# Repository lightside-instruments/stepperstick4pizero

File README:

stepperstick4pizero is an open hardware platform for FPGA
development published by Lightside Instruments AS.

The initial release stepperstick4pizero-1.0 includes schematic and PCB
design files for KiCAD.

The project is published by Lightside Instruments AS
under TAPR Open Hardware License. Read the LICENSE file
for details.

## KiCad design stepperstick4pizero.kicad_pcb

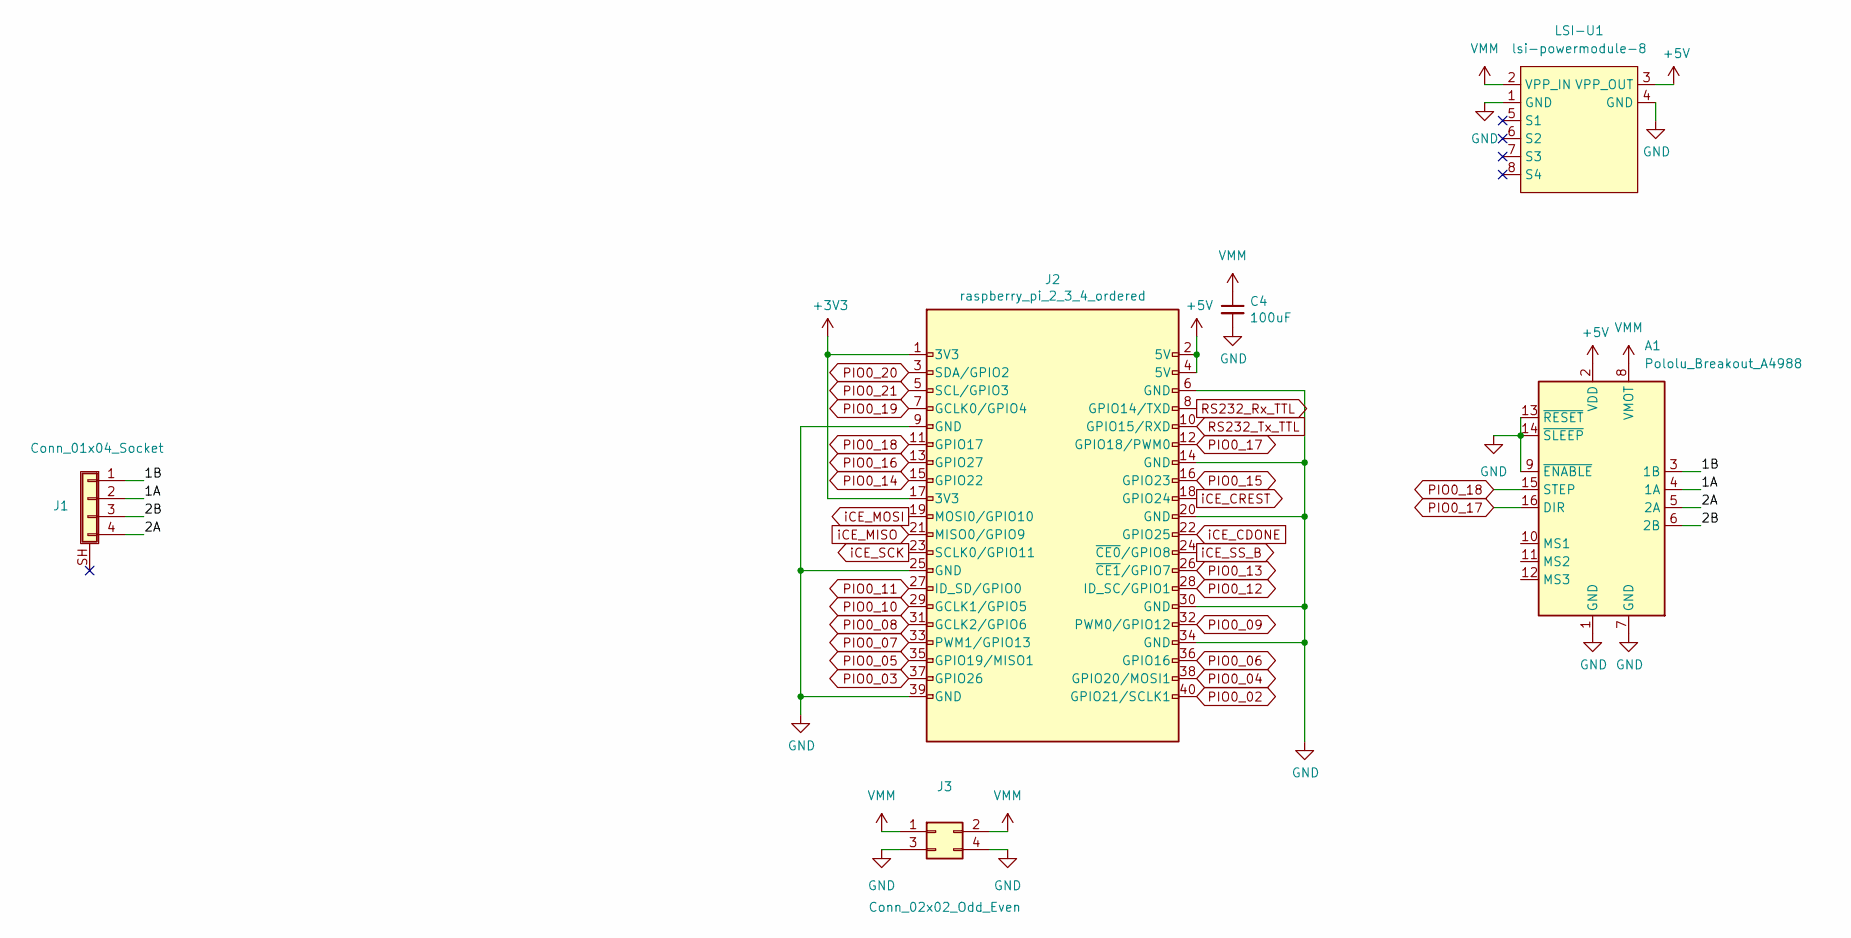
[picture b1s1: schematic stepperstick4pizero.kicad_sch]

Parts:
A1: Pololu_Breakout_A4988; Pololu_Breakout-16_15.2x20.3mm
C4: 100uF; C_Elec_6.3x7.7
J1: Conn_01x04_Socket; Amphenol_M8S-04PMMR-SF8001
J2: raspberry_pi_2_3_4_ordered; PinSocket_2x20_P2.54mm_Vertical_1_04mm
J3: Conn_02x02_Odd_Even; PinHeader_2x02_P2.54mm_Vertical
LSI-U1: lsi-powermodule-8

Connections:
+3V3: J2.1 (3V3), J2.17 (3V3)
+5V: A1.2 (VDD), J2.2 (5V), J2.4 (5V), LSI-U1.3 (VPP_OUT)
/1A: A1.4 (1A), J1.2
/1B: A1.3 (1B), J1.1
/2A: A1.5 (2A), J1.4
/2B: A1.6 (2B), J1.3
GND: A1.1 (GND), A1.7 (GND), A1.9 (~ENABLE), A1.13 (~RESET), A1.14 (~SLEEP), C4.2, J2.6 (GND), J2.9 (GND), J2.14 (GND), J2.20 (GND), J2.25 (GND), J2.30 (GND), J2.34 (GND), J2.39 (GND), J3.3, J3.4, LSI-U1.1 (GND), LSI-U1.4 (GND)
PIO0_02: J2.40 (GPIO21/SCLK1)
PIO0_03: J2.37 (GPIO26)
PIO0_04: J2.38 (GPIO20/MOSI1)
PIO0_05: J2.35 (GPIO19/MISO1)
PIO0_06: J2.36 (GPIO16)
PIO0_07: J2.33 (PWM1/GPIO13)
PIO0_08: J2.31 (GCLK2/GPIO6)
PIO0_09: J2.32 (PWM0/GPIO12)
PIO0_10: J2.29 (GCLK1/GPIO5)
PIO0_11: J2.27 (ID_SD/GPIO0)
PIO0_12: J2.28 (ID_SC/GPIO1)
PIO0_13: J2.26 (~CE1/GPIO7)
PIO0_14: J2.15 (GPIO22)
PIO0_15: J2.16 (GPIO23)
PIO0_16: J2.13 (GPIO27)
PIO0_17: A1.16 (DIR), J2.12 (GPIO18/PWM0)
PIO0_18: A1.15 (STEP), J2.11 (GPIO17)
PIO0_19: J2.7 (GCLK0/GPIO4)
PIO0_20: J2.3 (SDA/GPIO2)
PIO0_21: J2.5 (SCL/GPIO3)
RS232_Rx_TTL: J2.8 (GPIO14/TXD)
RS232_Tx_TTL: J2.10 (GPIO15/RXD)
VMM: A1.8 (VMOT), C4.1, J3.1, J3.2, LSI-U1.2 (VPP_IN)
iCE_CDONE: J2.22 (GPIO25)
iCE_CREST: J2.18 (GPIO24)
iCE_MISO: J2.21 (MISO0/GPIO9)
iCE_MOSI: J2.19 (MOSI0/GPIO10)
iCE_SCK: J2.23 (SCLK0/GPIO11)
iCE_SS_B: J2.24 (~CE0/GPIO8)

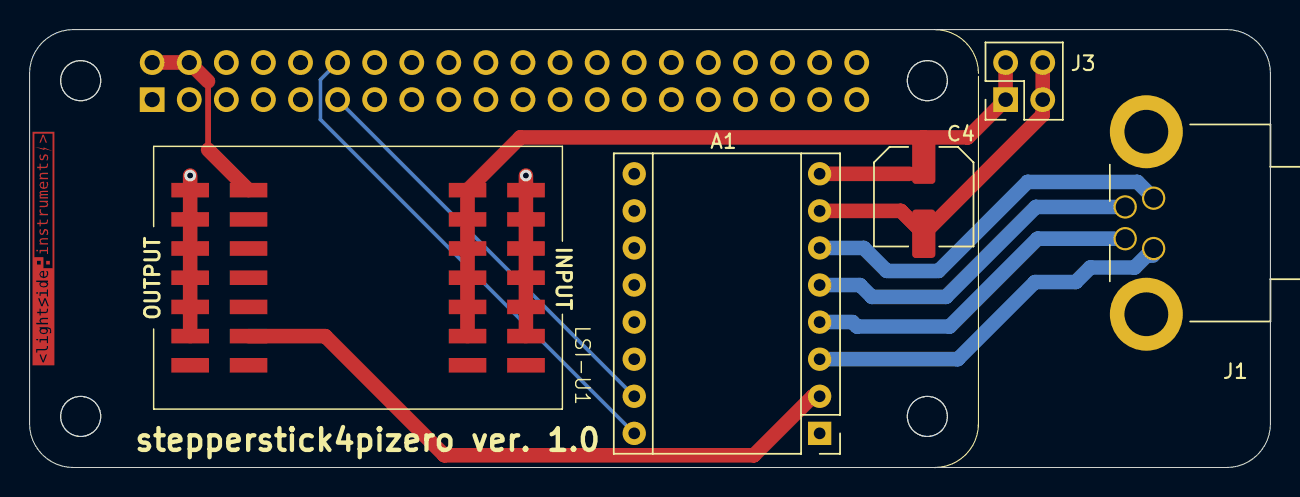
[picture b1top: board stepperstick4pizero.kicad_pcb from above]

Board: 4 copper layers, 85.0 x 30.0 mm, 7 parts (1 on the bottom side), 10 nets.

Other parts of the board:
svg2mod: G***; lsi-logo-16mm-fcu
